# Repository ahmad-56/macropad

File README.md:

<h1>AHMAD HASSAN'S MACROPAD</h1>
<h2>Process of making:</h2>
<p>I created this macropad using 8 switches, 1 rp2040, 1 oled display, 1 rotary encoder switch and 8 leds. This was my first hardware project and I enjoyed making it. In this project I used KiCad for designing the PCB which involved several steps including making the schematic and then designing and routing the PCB. As for the Case I used Fusion360. Lastly, I used kmk firmware for the keyboard’s Firmware. Overall the experience of using all softwares was quite smooth. The only time I did run into issues were when for example finding the correct symbol and footprint for the SK6812MINI-E and fixing the dimensions in the 3d model. Both of which I fixed.</p>
<h2>Firmware:</h2>
I used the kmk Firware for the entire keyboard.
<li>The Rotary Encoder changes volume. Pressing it wouldmute.</li>
<li>The 8 keys currently are used for different purposes but mainly 4 of them are arrow keys other contain print screen, delete, mute mic and close camera.</li>
<li>The OLED is </li>
<p>I might change features in future but that's it for now.</p>
<h2>BOM:</h2>
<li>1x XIAO RP2040</li>
<li>8x SK6812 MINI-E Leds</li>
<li>8x Cherry MX Switches</li>
<li>8x DSA Keycaps</li>
<li>9x 1N4148 DO-35 Diodes.</li>
<li>1x 0.91" 128x32 OLED Display</li>
<li>1x EC11 Rotary Encoder Switch</li>
<li>4x M3x16 Bolt</li>
<li>4x M3 Heatset</li>
<li>1x Case (2 printed parts - Top Case and Bottom Case)</li>
<br>
<h2>Schematic:</h2>

<h2>PCB:</h2>

<h2>3D Case:</h2>
<table>
  <tr>
    <td></td>
    <td></td>
    <td></td>
  </tr>
</table>

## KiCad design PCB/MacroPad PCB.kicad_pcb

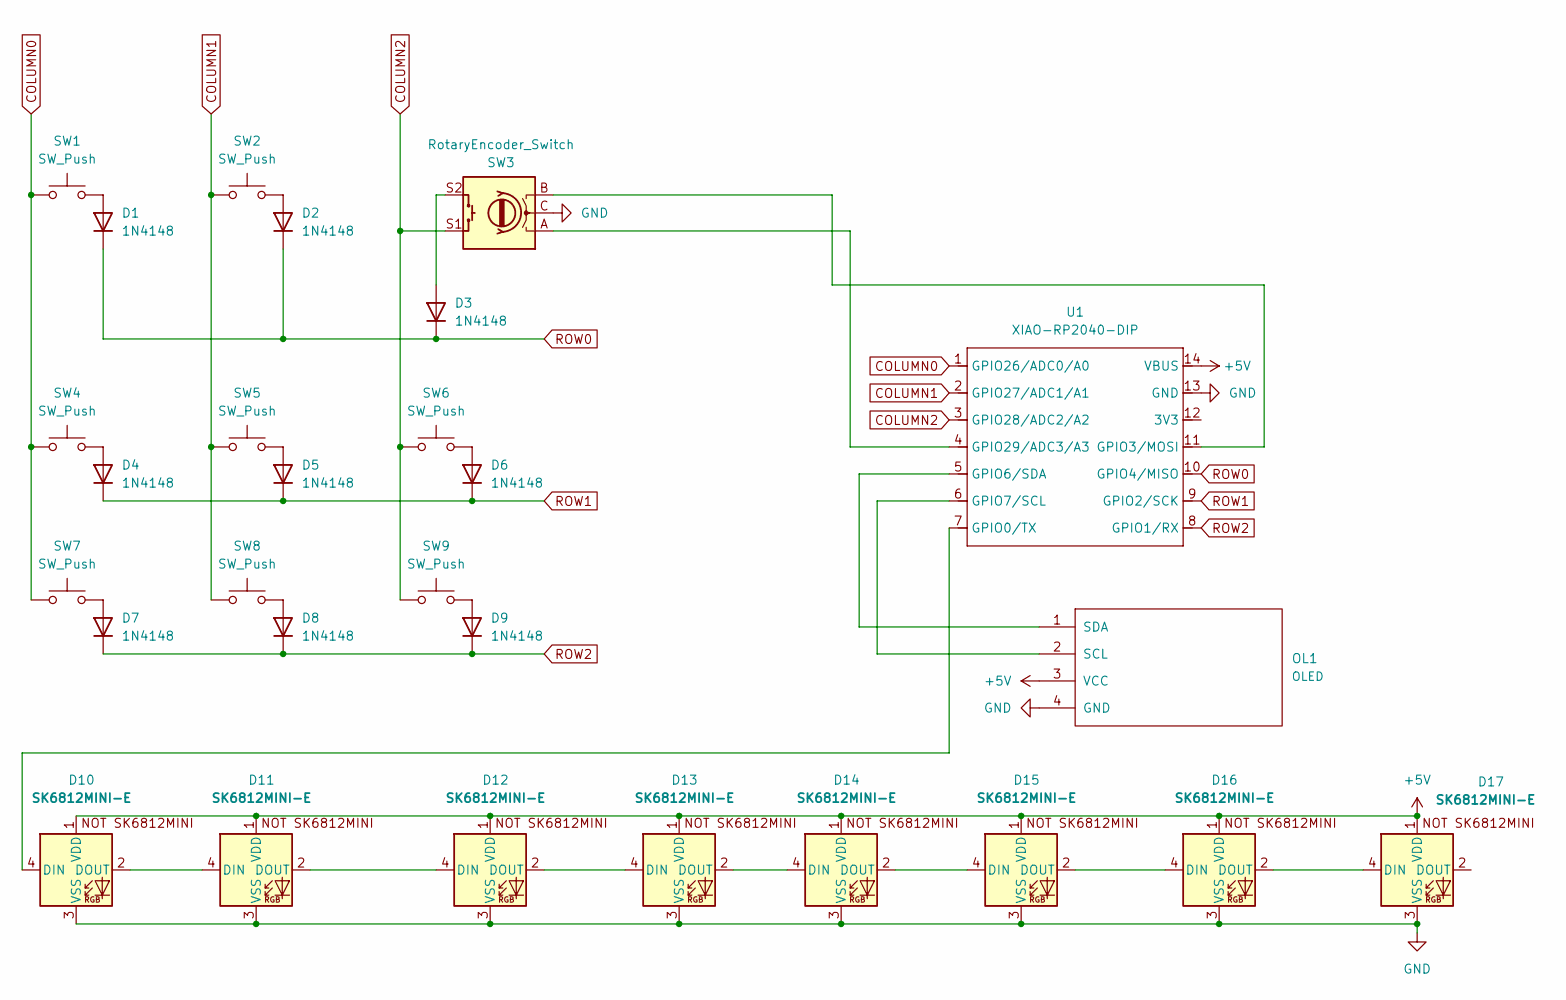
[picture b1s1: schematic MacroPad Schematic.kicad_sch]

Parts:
D1, D2, D3, D4, D5, D6, D7, D8, D9: 1N4148; D_DO-35_SOD27_P7.62mm_Horizontal
D10, D11, D12, D13, D14, D15, D16, D17: SK6812MINI-E; SK6812MINI-E_fixed
OL1: OLED; SSD1306-0.91-OLED-4pin-128x32
SW1, SW2, SW4, SW5, SW6, SW7, SW8, SW9: SW_Push; SW_Cherry_MX_1.00u_PCB
SW3: RotaryEncoder_Switch; RotaryEncoder_Alps_EC11E-Switch_Vertical_H20mm_MountingHoles
U1: XIAO-RP2040-DIP

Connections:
+5V: D10.1 (VDD), D11.1 (VDD), D12.1 (VDD), D13.1 (VDD), D14.1 (VDD), D15.1 (VDD), D16.1 (VDD), D17.1 (VDD), OL1.3 (VCC), U1.14 (VBUS)
COLUMN0: SW1.1, SW4.1, SW7.1, U1.1 (GPIO26/ADC0/A0)
COLUMN1: SW2.1, SW5.1, SW8.1, U1.2 (GPIO27/ADC1/A1)
COLUMN2: SW3.S1, SW6.1, SW9.1, U1.3 (GPIO28/ADC2/A2)
GND: D10.3 (VSS), D11.3 (VSS), D12.3 (VSS), D13.3 (VSS), D14.3 (VSS), D15.3 (VSS), D16.3 (VSS), D17.3 (VSS), OL1.4 (GND), SW3.C, U1.13 (GND)
unnamed: D1.2 (A), SW1.2
unnamed: D2.2 (A), SW2.2
unnamed: D3.2 (A), SW3.S2
unnamed: D4.2 (A), SW4.2
unnamed: D5.2 (A), SW5.2
unnamed: D6.2 (A), SW6.2
unnamed: D7.2 (A), SW7.2
unnamed: D8.2 (A), SW8.2
unnamed: D9.2 (A), SW9.2
unnamed: D10.4 (DIN), U1.7 (GPIO0/TX)
unnamed: D10.2 (DOUT), D11.4 (DIN)
unnamed: D11.2 (DOUT), D12.4 (DIN)
unnamed: D12.2 (DOUT), D13.4 (DIN)
unnamed: D13.2 (DOUT), D14.4 (DIN)
unnamed: D14.2 (DOUT), D15.4 (DIN)
unnamed: D15.2 (DOUT), D16.4 (DIN)
unnamed: D16.2 (DOUT), D17.4 (DIN)
unnamed: OL1.2 (SCL), U1.6 (GPIO7/SCL)
unnamed: OL1.1 (SDA), U1.5 (GPIO6/SDA)
unnamed: SW3.B, U1.11 (GPIO3/MOSI)
unnamed: SW3.A, U1.4 (GPIO29/ADC3/A3)
ROW0: D1.1 (K), D2.1 (K), D3.1 (K), U1.10 (GPIO4/MISO)
ROW1: D4.1 (K), D5.1 (K), D6.1 (K), U1.9 (GPIO2/SCK)
ROW2: D7.1 (K), D8.1 (K), D9.1 (K), U1.8 (GPIO1/RX)

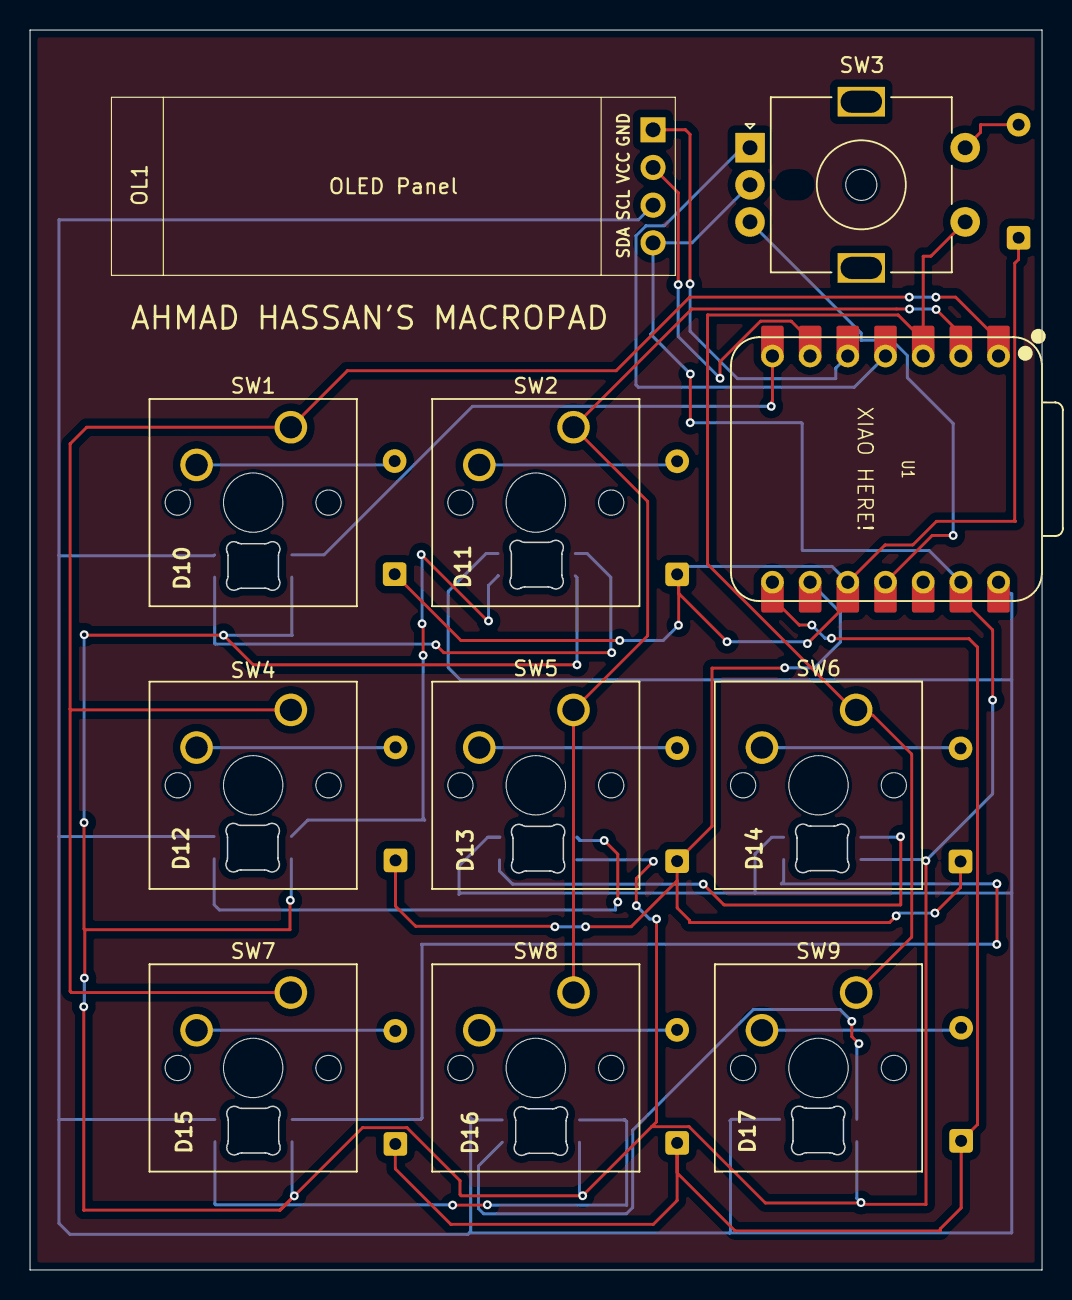
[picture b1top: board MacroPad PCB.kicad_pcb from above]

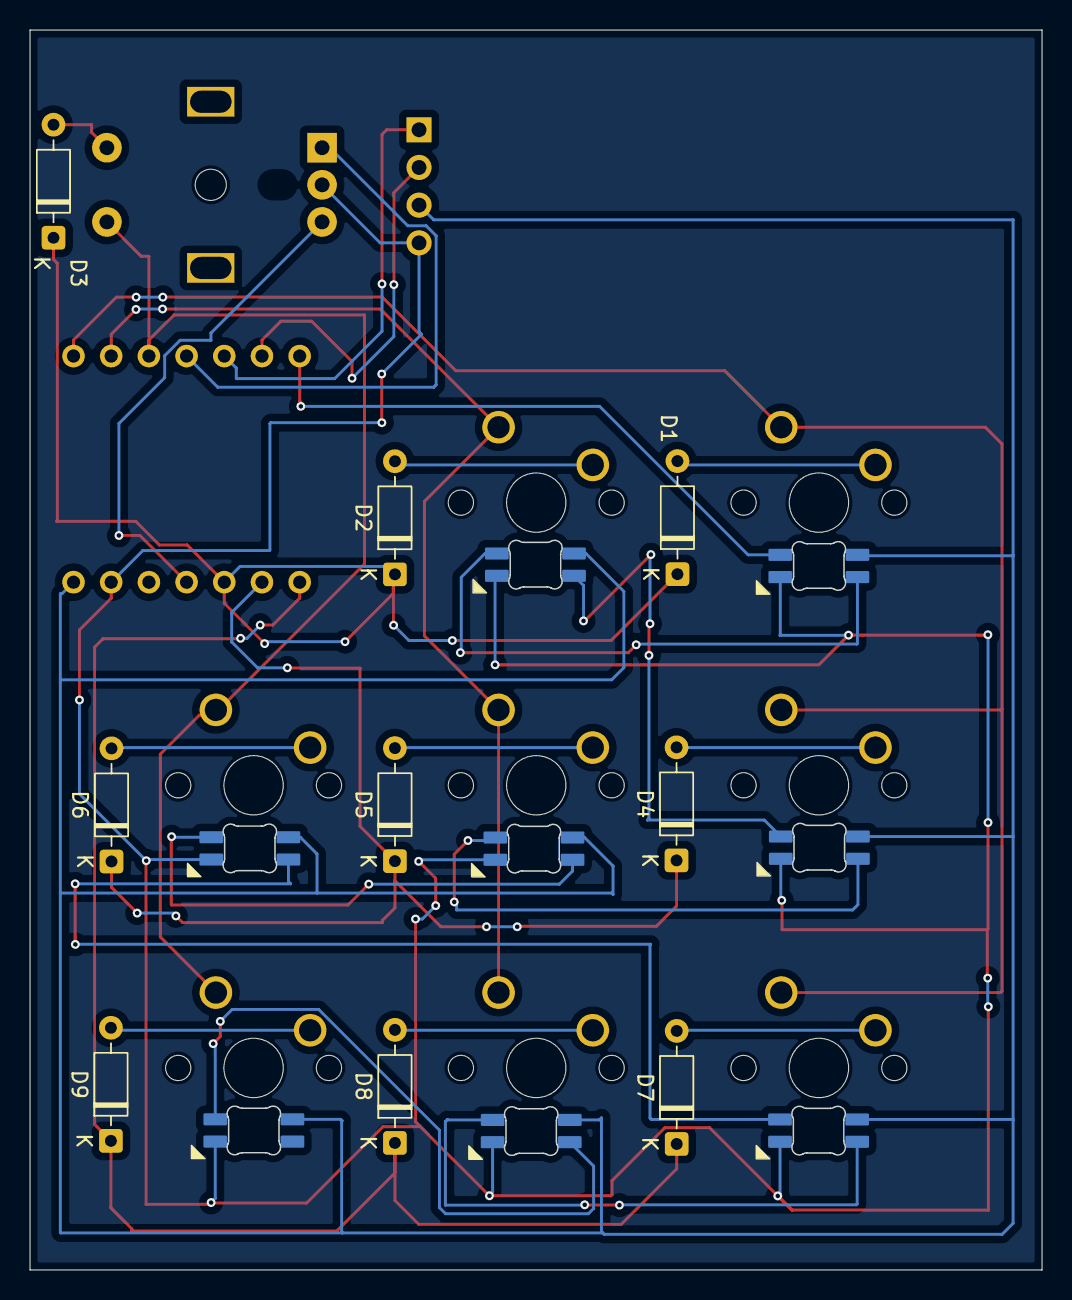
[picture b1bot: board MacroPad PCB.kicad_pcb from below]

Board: 2 copper layers, 68.2 x 83.5 mm, 28 parts (9 on the bottom side), 29 nets.

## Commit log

2026-01-07 folders added
2026-01-07 firmware and cad file added
2026-01-07 Update README with firmware details and future plans
    Corrected and clarified the firmware section and added a paragraph about future changes.
2026-01-08 3d added
